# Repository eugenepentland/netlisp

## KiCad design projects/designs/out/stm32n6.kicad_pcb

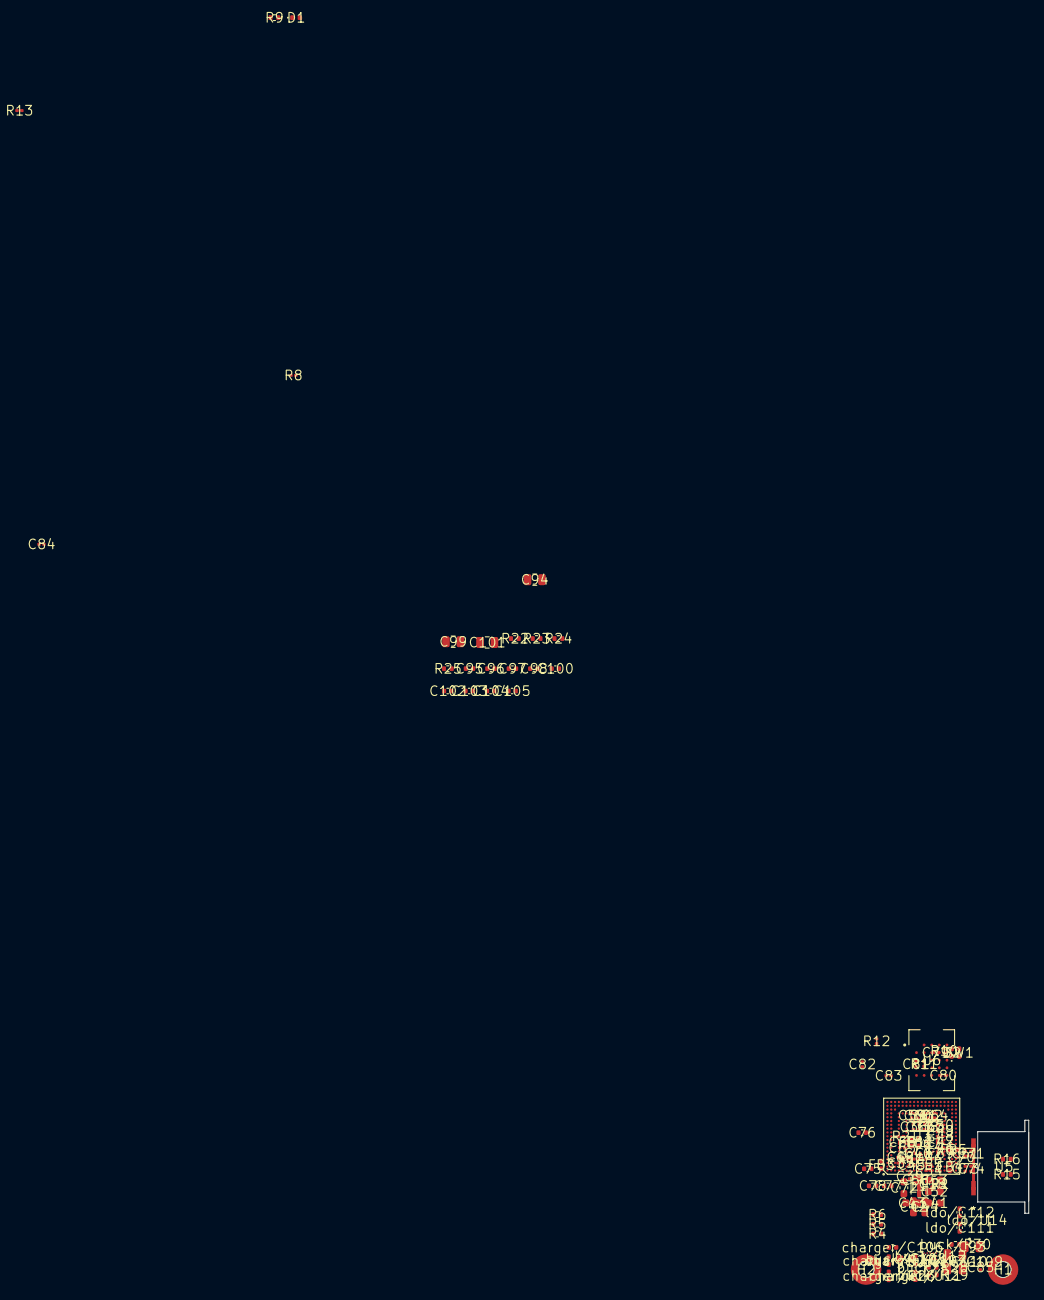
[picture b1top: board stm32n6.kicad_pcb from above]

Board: 2 copper layers, 6.7 x 12.2 mm, 112 parts (0 on the bottom side), 89 nets, no tracks yet.

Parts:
C18: 2.2nF; C_0402_1005Metric
C35, C36, C37, C38, C39, C40, C56, C57, C58, C59, C60, C61, C62, C63, C64, C65, C66, C67, C68, C69, C70, C74, C79, C80, C81, C82, C83, C84, C85: 100nF; C_0201_0603Metric
C41, C42, C43, C44: 15uF; C_0603_1608Metric
C45, C46, C47, C48, C49, C50, C51, C54, C55, C71, C73: 1uF; C_0201_0603Metric
C52, C53: 10uF; C_0603_1608Metric
C72: 4.7uF; C_0603_1608Metric
C75, C76: 10pF; C_0402_1005Metric
C77, C78: 6.8pF; C_0402_1005Metric
C93, C94, C99, C101: 10uF; C_0805_2012Metric
C95, C96, C97, C98, C100: 100nF; C_0402_1005Metric
C102, C103: 1uF; C_0402_1005Metric
C104, C105: 330pF; C_0402_1005Metric
D1: green; LED_0402_1005Metric
D2: PMEG2005AEA; d-0402
FB1, FB2, FB3, FB4, FB5: 600R@100MHz; FB_0402_1005Metric
H1, H2: A_Wurth_WA-SMSI_9774020633R
L1: 1uH; L_2016_Murata_DFE201610P
R1: 2R; R_0402_1005Metric
R2, R10, R11, R12, R13, R14: 10k; R_0201_0603Metric
R4, R5, R6: 33R; R_0402_1005Metric
R8: 200R; R_0201_0603Metric
R9: 330R; R_0402_1005Metric
R15, R16: 5.1k; R_0402_1005Metric
R22, R23, R24, R25: 25R; R_0402_1005Metric
SW1: 0R; R_0402_1005Metric
U3: BGA223C50P19X19_1000X1000X100
U5: USB4510-03-1-A_GCT
U6: BGA24C100P5X5_800X600X120
buck/C108: 10uF; C_0603_1608Metric
buck/C109, buck/C110: 47uF; C_0805_2012Metric
buck/R28: 511k; R_0402_1005Metric
buck/R29: 91k; R_0402_1005Metric
buck/R30: 100k; R_0402_1005Metric
buck/U12: dsbga-15
charger/C106, charger/C107: 4.7uF; C_0402_1005Metric
charger/R26: 2k; R_0402_1005Metric
charger/R27: 1k; R_0402_1005Metric
charger/U11: orange; LED_0402_1005Metric
ldo/C111, ldo/C112: 1uF; C_0402_1005Metric
ldo/U14: SOT95P280X145-5N

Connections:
ADC_AIN1N: C104.2, R23.2
ADC_AIN1P: C104.1, R22.2
ADC_AIN2N: C105.2, R25.2
ADC_AIN2P: C105.1, R24.2
ADC_REFOUT1: C98.1, C99.1
ADC_REFOUT2: C100.1, C101.1
ADC_REFRTN1: C98.2, C99.2
ADC_REFRTN2: C100.2, C101.2
BOOT0: R13.1, U3.F4
CC1: R15.1, U5.A5
CC2: R16.1, U5.B5
FLASH_CLK: U3.U19, U6.B2
FLASH_DQS: U3.R19, U6.C3
FLASH_IO0: U3.T19, U6.D3
FLASH_IO1: U3.P19, U6.D2
FLASH_IO2: U3.V19, U6.C4
FLASH_IO3: U3.U18, U6.D4
FLASH_IO4: U3.V18, U6.D5
FLASH_IO5: U3.T18, U6.E3
FLASH_IO6: U3.R18, U6.E2
FLASH_IO7: U3.P18, U6.E1
FLASH_NCS: R11.1, U3.P16, U6.C2
FLASH_RESET: D2.2, R10.1, U6.A4
GND: C35.2, C36.2, C37.2, C38.2, C39.2, C40.2, C41.2, C42.2, C43.2, C44.2, C45.2, C46.2, C47.2, C48.2, C49.2, C50.2, C51.2, C52.2, C53.2, C54.2, C55.2, C56.2, C57.2, C58.2, C59.2, C60.2, C61.2, C62.2, C63.2, C64.2, C65.2, C66.2, C67.2, C68.2, C69.2, C70.2, C71.2, C72.2, C73.2, C74.2, C75.2, C76.2, C77.2, C78.2, C79.2, C80.2, C81.2, C82.2, C83.2, C84.2, C85.2, C93.2, C94.2, C95.2, C96.2, C97.2, C102.2, C103.2, D1.2, H1.1, H2.1, R1.2, R8.2, R13.2, R14.2, R15.2, R16.2, SW1.2, U3.A19, U3.F12, U3.G6, U3.H2, U3.H14, U3.J1, U3.J2, U3.J3, U3.J4, U3.J5, U3.N6, U3.N16, U3.P8, U3.P12, U3.P14, U3.V2, U3.W1, U3.W19, U5.A1-B12, U5.B1-A12, U6.B3, U6.C1, U6.E5
LED_NET: D1.1, R9.2
NRST: C35.1, D2.1, SW1.1, U3.F2
OSC32_IN: C77.1, U3.E1
OSC32_OUT: C78.1, U3.D1
OSC_IN: C75.1, U3.A5
OSC_OUT: C76.1, U3.B5
PA6: R14.1, U3.T10
PG10: R9.1, U3.T12
PSRAM_NCS: R12.1, U3.F16
PWR_ON: R2.1, U3.G4
SNUB1: C18.2, R1.1
SWCLK_MCU: R5.1, U3.V7
SWDIO_MCU: R4.1, U3.W7
SWO_MCU: R6.1, U3.T14
TXRTUNE: R8.1, U3.E2
USB_CONN_DN: U5.A7, U5.B7
USB_CONN_DP: U5.A6, U5.B6
V1P8: C97.1, FB1.1, FB2.1, FB3.1, FB4.1, FB5.1, R10.2, R11.2, R12.2
V1P8.U3.H1: C58.1, U3.H1
V1P8.U3.H16: C59.1, U3.H16
V1P8.U3.J16: C60.1, U3.J16
V1P8.U3.K16: C61.1, U3.K16
V1P8.U3.L16: C62.1, U3.L16
V1P8.U3.M14: C63.1, U3.M14
V1P8.U3.M16: C64.1, U3.M16
V1P8.U6.B4: C79.1, U6.B4
V1P8.U6.D1: C81.1, U6.D1
V1P8.U6.E4: C80.1, U6.E4
V08CAP.U3.G1: C72.1, U3.G1
VBUS: U5.A4-B9, U5.B4-A9
VDD: C84.1, R2.2, U3.C3, U3.L2, U3.L3, U3.L4, U3.L5
VDD.U3.F1: C39.1, U3.F1
VDD.U3.F7: C65.1, U3.F7
VDD.U3.F8: C66.1, U3.F8
VDD.U3.J14: C36.1, U3.J14
VDD.U3.K14: C37.1, U3.K14
VDD.U3.L1: C52.1, C53.1, C54.1, C55.1, C56.1, C57.1, U3.L1
VDD.U3.L14: C38.1, U3.L14
VDD.U3.W2: C73.1, C74.1, U3.W2
VDD.U9.VDD_1: C93.1, C94.1, C95.1, C96.1
VDDA18ADC: C69.1, FB4.2, U3.P6
VDDA18AON: FB1.2, U3.A1
VDDA18AON.U3.H6: C40.1, U3.H6
VDDA18CSI: C70.1, FB5.2, U3.V6
VDDA18PLL: C67.1, FB2.2, U3.M6
VDDA18USB: C68.1, FB3.2, U3.D4
VDDCORE.U3.G2: C45.1, U3.G2
VDDCORE.U3.P7: C41.1, C42.1, C43.1, C44.1, C46.1, U3.P7
VDDCORE.U3.P9: C47.1, U3.P9
VDDCORE.U3.P10: C48.1, U3.P10
VDDCORE.U3.P11: C49.1, U3.P11
VDDCORE.U3.P13: C50.1, U3.P13
VDDCORE.U3.W6: C51.1, C71.1, U3.W6
VLXSMPS: C18.1, L1.1, U3.K1, U3.K2, U3.K3, U3.K4, U3.K5
buck/FB: buck/R28.2, buck/R29.1, buck/U12.D1
buck/GND: buck/C108.2, buck/C109.2, buck/C110.2, buck/R29.2, buck/U12.B1, buck/U12.C1, buck/U12.C2, buck/U12.C3
buck/PG: buck/R30.1, buck/U12.E1
buck/SW_L1: buck/U12.B2, buck/U12.B3
buck/SW_L2: buck/U12.D2, buck/U12.D3
buck/VIN: buck/U12.A1, buck/U12.A2, buck/U12.A3
buck/VOUT: buck/R28.1, buck/R30.2, buck/U12.E2, buck/U12.E3
buck/VOUT.U12.VOUT_1: buck/C109.1, buck/C110.1
charger/CHG_LED: charger/R27.2, charger/U11.1
charger/GND: charger/C106.2, charger/C107.2, charger/R26.2
ldo/GND: ldo/C111.2, ldo/C112.2

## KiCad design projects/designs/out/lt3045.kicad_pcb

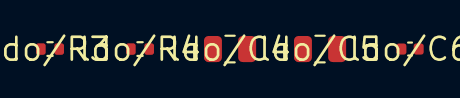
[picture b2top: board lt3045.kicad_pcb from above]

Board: 2 copper layers, 5 parts (0 on the bottom side), 3 nets, no tracks yet.

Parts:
ldo/C4: 4.7uF; C_0805_2012Metric
ldo/C5: 10uF; C_0805_2012Metric
ldo/C6: 0.47uF; C_0402_1005Metric
ldo/R3: 60k; R_0402_1005Metric
ldo/R4: 300; R_0402_1005Metric

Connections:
ldo/GND: ldo/C4.2, ldo/C5.2
ldo/SET: ldo/C6.1, ldo/R3.1
ldo/SET_GND: ldo/C6.2, ldo/R3.2

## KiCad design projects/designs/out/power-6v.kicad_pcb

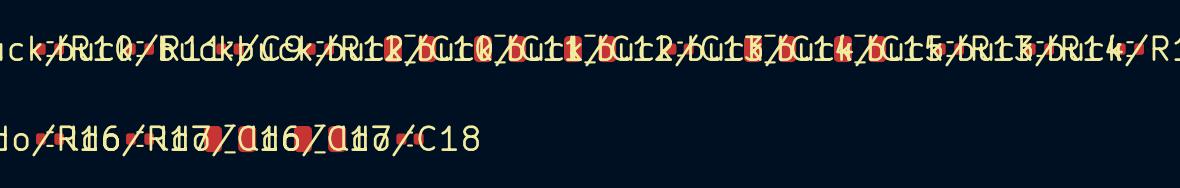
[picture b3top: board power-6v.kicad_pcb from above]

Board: 2 copper layers, 18 parts (0 on the bottom side), 7 nets, no tracks yet.

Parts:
buck/C9: 22pF; C_0402_1005Metric
buck/C10, buck/C11, buck/C12: 10uF; C_0805_2012Metric
buck/C13: 100nF; C_0402_1005Metric
buck/C14, buck/C15: 22uF; C_0805_2012Metric
buck/R10: 320k; R_0402_1005Metric
buck/R11: 30k; R_0402_1005Metric
buck/R12: 0R; R_0402_1005Metric
buck/R13: 18k; R_0402_1005Metric
buck/R14: 100k; R_0402_1005Metric
buck/R15: 820; R_0402_1005Metric
ldo/C16: 4.7uF; C_0805_2012Metric
ldo/C17: 10uF; C_0805_2012Metric
ldo/C18: 0.47uF; C_0402_1005Metric
ldo/R16: 60k; R_0402_1005Metric
ldo/R17: 300; R_0402_1005Metric

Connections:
buck/7V: buck/C9.1, buck/C14.1, buck/C15.1, buck/R10.1, buck/R14.2, buck/R15.1
buck/FB: buck/C9.2, buck/R10.2, buck/R11.1
buck/GND: buck/C10.2, buck/C11.2, buck/C12.2, buck/C13.2, buck/C14.2, buck/C15.2, buck/R11.2, buck/R12.2, buck/R13.2
buck/VIN: buck/C10.1, buck/C11.1, buck/C12.1, buck/C13.1
ldo/GND: ldo/C16.2, ldo/C17.2
ldo/SET: ldo/C18.1, ldo/R16.1
ldo/SET_GND: ldo/C18.2, ldo/R16.2

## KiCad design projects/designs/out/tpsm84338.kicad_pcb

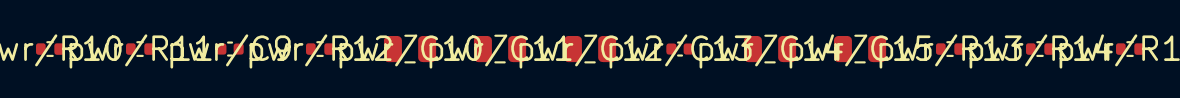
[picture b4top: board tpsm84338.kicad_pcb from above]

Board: 2 copper layers, 13 parts (0 on the bottom side), 4 nets, no tracks yet.

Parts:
pwr/C9: 22pF; C_0402_1005Metric
pwr/C10, pwr/C11, pwr/C12: 10uF; C_0805_2012Metric
pwr/C13: 100nF; C_0402_1005Metric
pwr/C14, pwr/C15: 22uF; C_0805_2012Metric
pwr/R10: 220k; R_0402_1005Metric
pwr/R11: 47k; R_0402_1005Metric
pwr/R12: 0R; R_0402_1005Metric
pwr/R13: 18k; R_0402_1005Metric
pwr/R14: 100k; R_0402_1005Metric
pwr/R15: 1k; R_0402_1005Metric

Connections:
pwr/3.4085V: pwr/C9.1, pwr/C14.1, pwr/C15.1, pwr/R10.1, pwr/R14.2, pwr/R15.1
pwr/FB: pwr/C9.2, pwr/R10.2, pwr/R11.1
pwr/GND: pwr/C10.2, pwr/C11.2, pwr/C12.2, pwr/C13.2, pwr/C14.2, pwr/C15.2, pwr/R11.2, pwr/R12.2, pwr/R13.2
pwr/VIN: pwr/C10.1, pwr/C11.1, pwr/C12.1, pwr/C13.1

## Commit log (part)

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2026-06-11 fix(placement): ind-* refdes prefix, decided series-part rotations, pinned heatmap scale
    Three fixes from the tps631000-rail investigation (auto layout kept the
    buck-boost inductor at rot 0 with one LX leg routing the long way round;
    dragging one cap re-tinted every other part in the blame heatmap):
    - componentPrefix: map ind-* families (ind-2016, ind-0603, …) to the L
    refdes prefix like the exact "ind" family, xfl* and ferrite* already
    were. A U-prefixed inductor was classified as a *hub*: its rotation was
2026-06-18 feat(placement): rough seed minimizes ratsnest crossings (cluster + polish)
    The pad-anchored rough seed anchored every part to the IC independently, so
    a subsystem whose parts don't all touch the IC (a TCXO wired only through its
    caps; a series R + its cap) got torn apart and its long airwires crossed the
    whole board. Measured on lmk05318b-clock: 185 crossings, 96% inter-net.
    Two-phase fix (185 → 137 → 72 crossings, −61%, still a legible ring):
    1. Cluster connected subsystems (buildClusters): union-find over non-hub parts
